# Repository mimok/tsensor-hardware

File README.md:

# tsensor-hardware
Kicad project of the Tsensor board

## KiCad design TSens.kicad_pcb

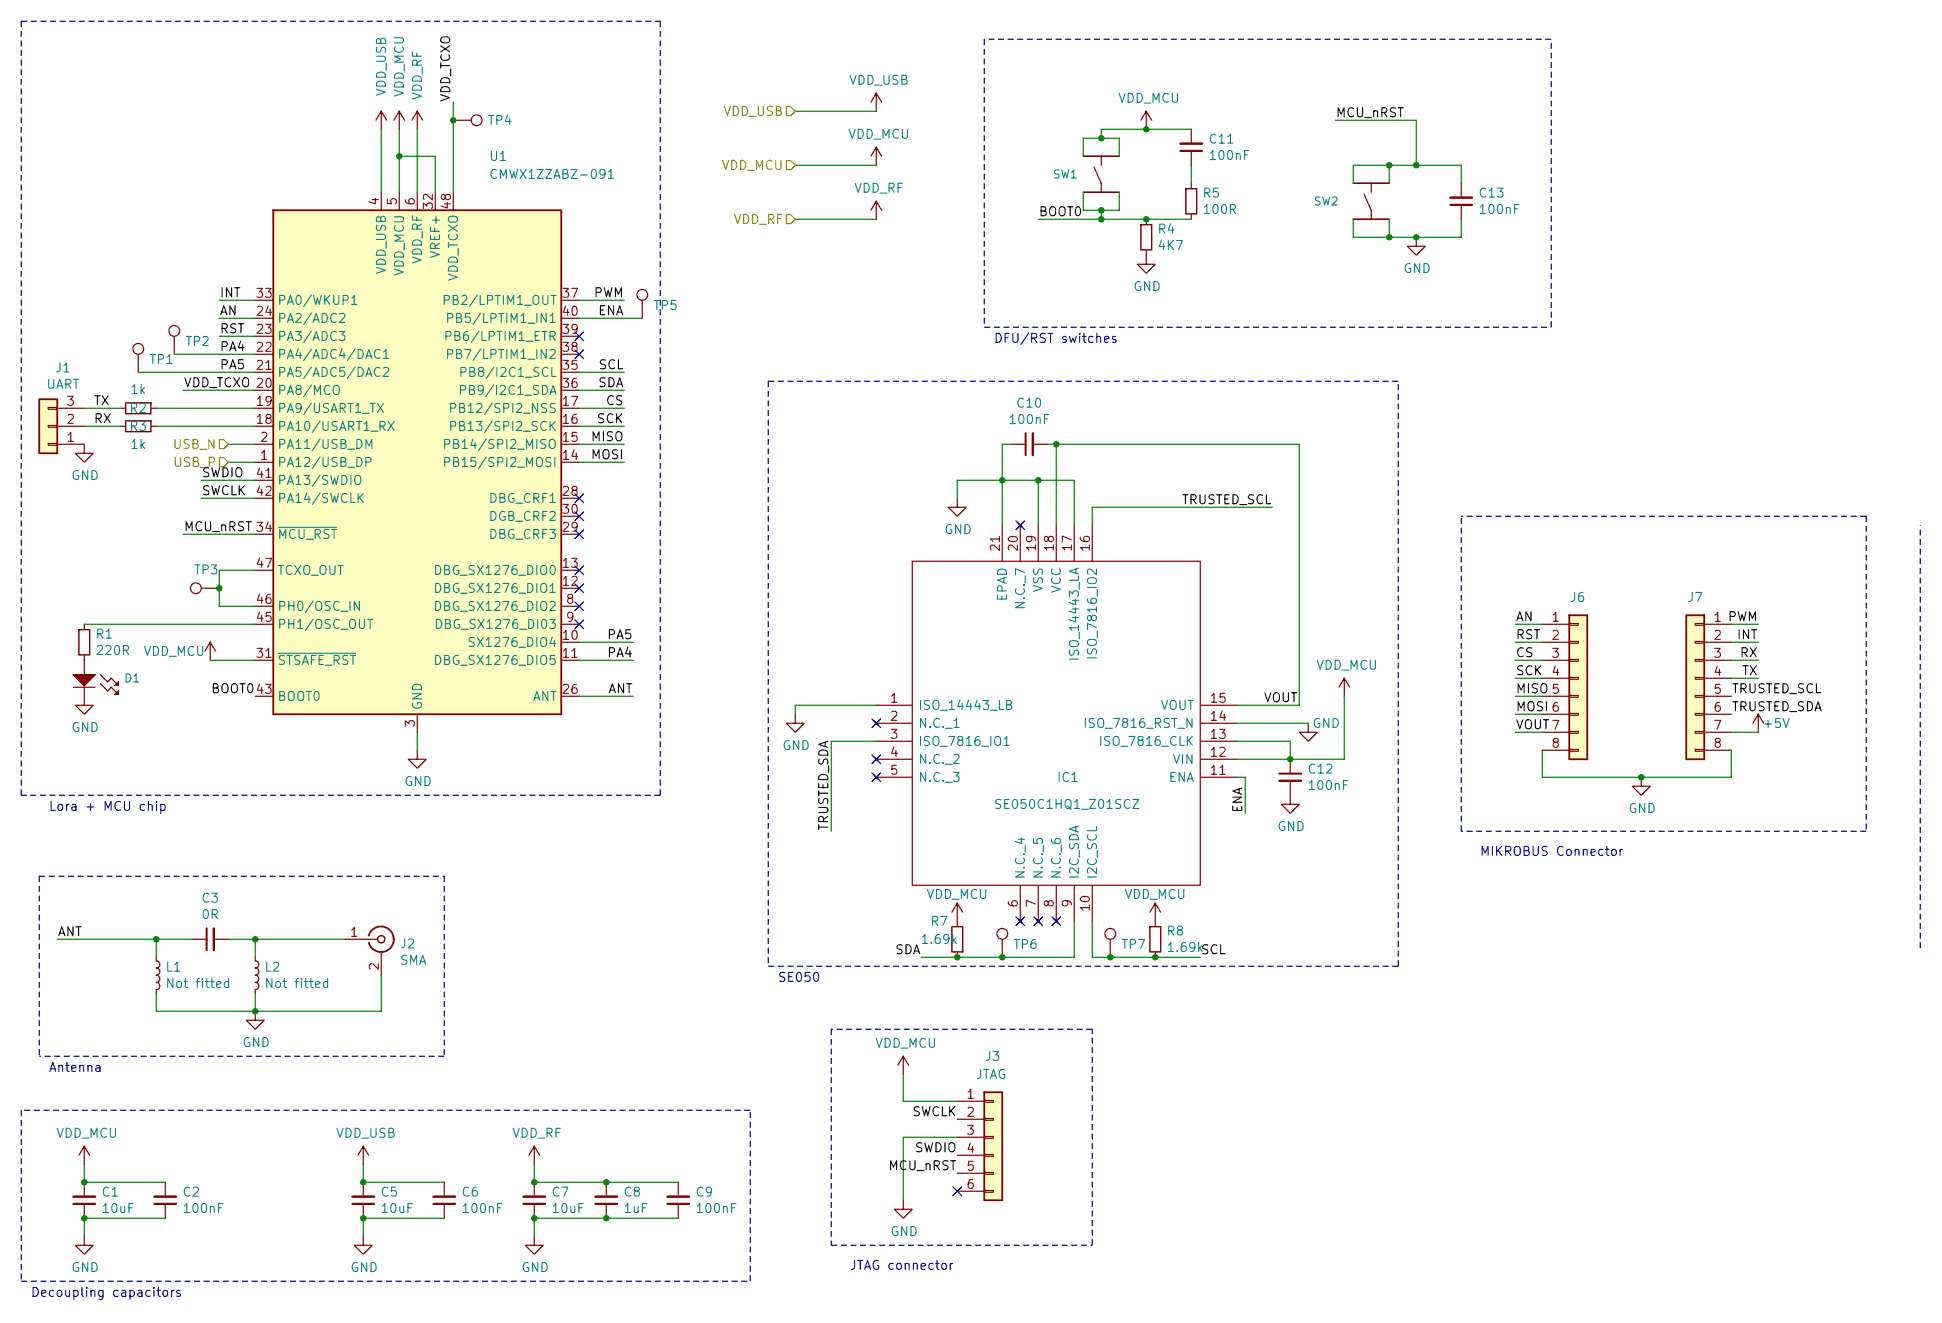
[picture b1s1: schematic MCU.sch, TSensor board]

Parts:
C1, C5, C7: 10uF; C_0603; Manufacturer_Part_Number GRM188R60J106KE47D; Mouser Part Number 81-GRM188R60J106KE7D
C2, C6, C9, C10, C11, C12, C13: 100nF; C_0603; Manufacturer_Part_Number 885012206020; Mouser Part Number 710-885012206020
C3: 0R; R_0603; Manufacturer_Part_Number RC0603JR-070RL; Mouser Part Number 603-RC0603JR-070RL
C8: 1uF; C_0603; Manufacturer_Part_Number C0603C105K8RACTU; Mouser Part Number 80-C0603C105K8RACTU
D1: LED_SINGLE-0603-RED; MF_LEDs-LED0603
IC1: SE050C1HQ1_Z01SCZ; QFN40P300X300X33-21N-D; Manufacturer_Part_Number SE050C1HQ1/Z01SCZ; Mouser Part Number 771-SE050C1HQ1Z01SCZ
J1: UART; PinHeader_1x03_P2.54mm_Vertical; Manufacturer_Part_Number M20-9990346; Mouser Part Number 855-M20-9990346
J2: SMA; SMA_Samtec_SMA-J-P-X-ST-EM1_EdgeMount; Manufacturer_Part_Number SMA-J-P-H-ST-EM1; Mouser Part Number 200-SMAJPHSTEM1
J3: JTAG; PinHeader_1x06_P2.54mm_Vertical; Manufacturer_Part_Number M20-9990646; Mouser Part Number 855-M20-9990646
J6, J7: Conn_01x08; PinSocket_1x08_P2.54mm_Vertical
L1, L2: Not fitted; L_0603
R1: 220R; R_0603; Manufacturer_Part_Number CRCW0603750RJNEA; Mouser Part Number 71-CRCW0603J-750-E3
R2, R3: 1k; R_0603; Manufacturer_Part_Number CRCW06031K00JNEAC; Mouser Part Number 71-CRCW06031K00JNEAC
R4: 4K7; R_0603; Manufacturer_Part_Number CRCW06034K70JNEAC; Mouser Part Number 71-CRCW06034K70JNEAC
R5: 100R; R_0603; Manufacturer_Part_Number CRCW0603100RJNEAC; Mouser Part Number 71-CRCW0603100RJNEAC
R7, R8: 1.69k; R_0603
SW1, SW2: TACT_4.2MM; MF_Switches-TACT4.2MM
TP1, TP2, TP3, TP4, TP5, TP6, TP7: TestPoint; TestPoint_Pad_D1.0mm
U1: CMWX1ZZABZ-091; MODULE_CMWX1ZZABZ-091; Manufacturer_Part_Number CMWX1ZZABZ-091; Mouser Part Number 81-CMWX1ZZABZ-091

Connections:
+3V3: C1.2, C2.2, C5.2, C6.2, C11.2, C12.1, IC1.12 (VIN), IC1.13 (ISO_7816_CLK), J3.1, R7.2, R8.1, SW1.1, SW1.2, U1.4 (VDD_USB), U1.5 (VDD_MCU), U1.31 (~STSAFE_RST), U1.32 (VREF+); also elsewhere on the board
+5V: J7.7; also elsewhere on the board
/MCU/AN: J6.1, U1.24 (PA2/ADC2)
/MCU/ANT: C3.1, L1.1, U1.26 (ANT)
/MCU/BOOT0: R4.1, R5.2, SW1.3, SW1.4, U1.43 (BOOT0)
/MCU/CS: J6.3, U1.17 (PB12/SPI2_NSS)
/MCU/ENA: IC1.11 (ENA), TP5.1, U1.40 (PB5/LPTIM1_IN1)
/MCU/INT: J7.2, U1.33 (PA0/WKUP1)
/MCU/MCU_nRST: C13.2, J3.5, SW2.1, SW2.2, U1.34 (~MCU_RST)
/MCU/MISO: J6.5, U1.15 (PB14/SPI2_MISO)
/MCU/MOSI: J6.6, U1.14 (PB15/SPI2_MOSI)
/MCU/PA4: TP2.1, U1.11 (DBG_SX1276_DIO5), U1.22 (PA4/ADC4/DAC1)
/MCU/PA5: TP1.1, U1.10 (SX1276_DIO4), U1.21 (PA5/ADC5/DAC2)
/MCU/PWM: J7.1, U1.37 (PB2/LPTIM1_OUT)
/MCU/RST: J6.2, U1.23 (PA3/ADC3)
/MCU/RX: J1.2, J7.3, R3.2
/MCU/SCK: J6.4, U1.16 (PB13/SPI2_SCK)
/MCU/SCL: IC1.10 (I2C_SCL), R8.2, TP7.1, U1.35 (PB8/I2C1_SCL)
/MCU/SDA: IC1.9 (I2C_SDA), R7.1, TP6.1, U1.36 (PB9/I2C1_SDA)
/MCU/SWCLK: J3.2, U1.42 (PA14/SWCLK)
/MCU/SWDIO: J3.4, U1.41 (PA13/SWDIO)
/MCU/TRUSTED_SCL: IC1.16 (ISO_7816_IO2), J7.5
/MCU/TRUSTED_SDA: IC1.3 (ISO_7816_IO1), J7.6
/MCU/TX: J1.3, J7.4, R2.2
/MCU/USB_N: U1.2 (PA11/USB_DM); also elsewhere on the board
/MCU/USB_P: U1.1 (PA12/USB_DP); also elsewhere on the board
/MCU/VDD_TCXO: TP4.1, U1.20 (PA8/MCO), U1.48 (VDD_TCXO)
/MCU/VOUT: C10.2, IC1.15 (VOUT), IC1.18 (VCC), J6.7
GND: C1.1, C2.1, C5.1, C6.1, C7.1, C8.1, C9.1, C10.1, C12.2, C13.1, D1.CATH (CATHODE), IC1.1 (ISO_14443_LB), IC1.14 (ISO_7816_RST_N), IC1.17 (ISO_14443_LA), IC1.19 (VSS), IC1.21 (EPAD), J1.1, J2.2 (Ext), J3.3, J6.8, J7.8, L1.2, L2.2, R4.2, SW2.3, SW2.4, U1.3 (GND), U1.7 (GND), U1.25 (GND), U1.27 (GND), U1.44 (GND), U1.49 (GND), U1.50 (GND), U1.51 (GND), U1.52 (GND), U1.53 (GND), U1.54 (GND), U1.55 (GND), U1.56 (GND), U1.57 (GND); also elsewhere on the board
unnamed: C3.2, J2.1 (In), L2.1
unnamed: C11.1, R5.1
unnamed: D1.ANOD (ANODE), R1.2
unnamed: R1.1, U1.45 (PH1/OSC_OUT)
unnamed: R2.1, U1.19 (PA9/USART1_TX)
unnamed: R3.1, U1.18 (PA10/USART1_RX)
unnamed: TP3.1, U1.46 (PH0/OSC_IN), U1.47 (TCXO_OUT)
VDD_RF: C7.2, C8.2, C9.2, U1.6 (VDD_RF); also elsewhere on the board

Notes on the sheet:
DFU/RST switches
Decoupling capacitors
MIKROBUS Connector
JTAG connector
Antenna
SE050
Lora + MCU chip

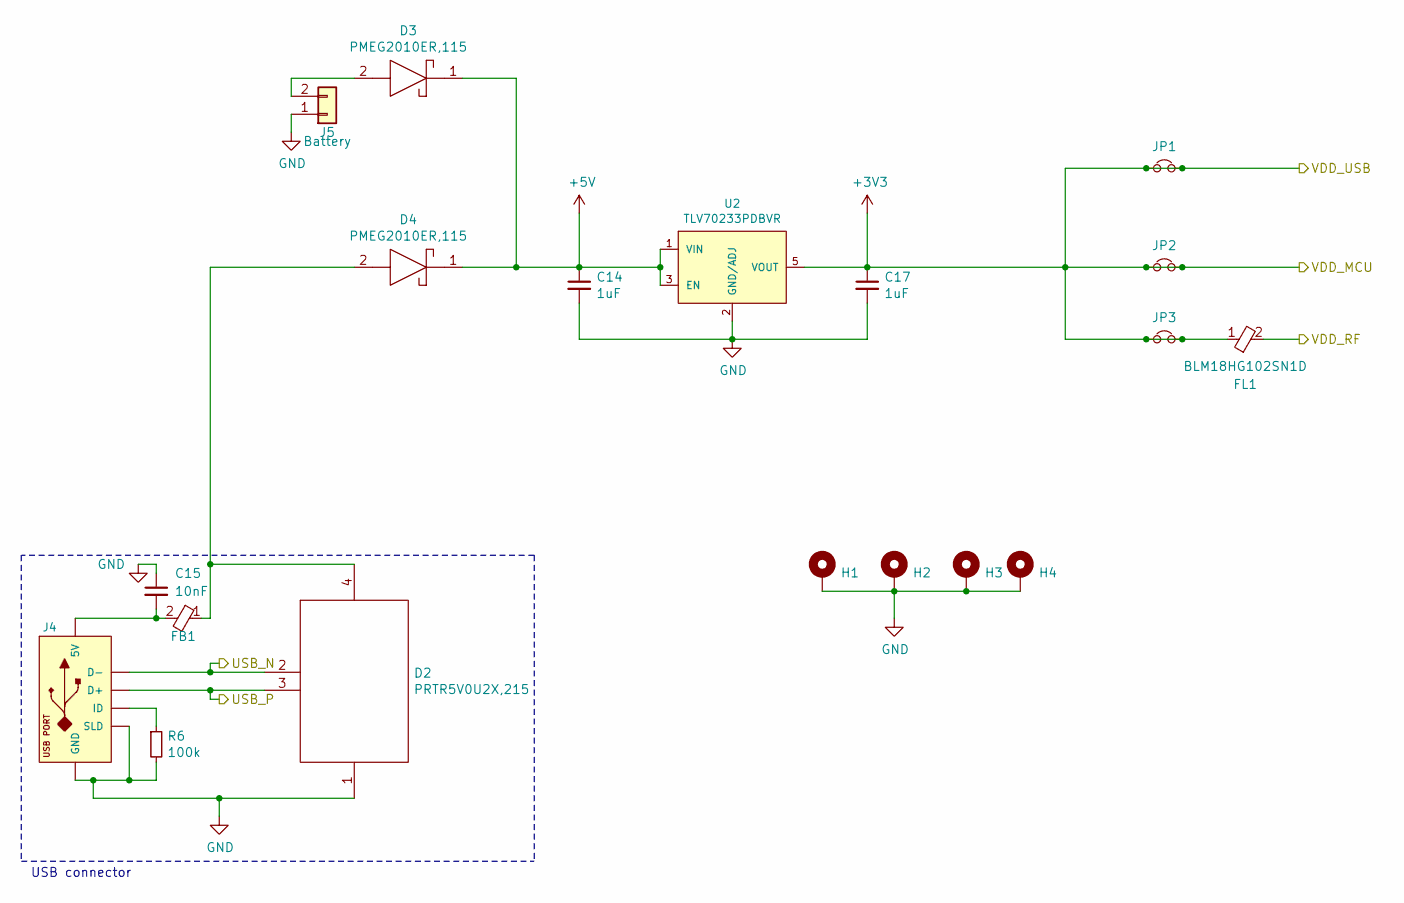
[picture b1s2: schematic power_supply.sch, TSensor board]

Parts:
C14, C17: 1uF; C_0603; Manufacturer_Part_Number C0603C105K8RACTU; Mouser Part Number 80-C0603C105K8RACTU
C15: 10nF; C_0603; Manufacturer_Part_Number 885012206014; Mouser Part Number 710-885012206014
D2: PRTR5V0U2X,215; SOT-143B; Mouser Part Number 771-PRTR5V0U2X-T/R
D3, D4: PMEG2010ER,115; SODFL3517X110N; Mouser Part Number 771-PMEG2010ER115
FB1: BK0603HS330-T; BEADC0603X33N; Mouser Part Number 963-BK0603HS330-T
FL1: BLM18HG102SN1D; BEADC1608X95N; Mouser Part Number 81-BLM11HA102SG
H1, H2, H3, H4: MountingHole_Pad; MountingHole_2.2mm_M2
J4: USB_MICRO_RIGHT; MF_Connectors-MICROUSB-RIGHT
J5: Battery; JST_PH_B2B-PH-SM4-TB_02x2.00mm_Straight; Manufacturer_Part_Number B2B-PH-SM4-TB(LF)(SN)
JP1, JP2, JP3: Jumper_NC_Small; PinHeader_1x02_P2.54mm_Vertical; Manufacturer_Part_Number M20-9990246; Mouser Part Number 855-M20-9990246
R6: 100k; R_0603; Manufacturer_Part_Number CRCW0603100KJNEAC; Mouser Part Number 71-CRCW0603100KJNEAC
U2: TLV70233PDBVR; MF_IC_Power-SOT-23-5

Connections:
+3V3: C17.1, FL1.1, JP1.1, JP1.2, JP2.1, JP2.2, JP3.1, JP3.2, U2.5 (VOUT); also elsewhere on the board
+5V: C14.1, D3.1, D4.1, U2.1 (VIN), U2.3 (EN); also elsewhere on the board
/MCU/USB_N: D2.2, J4.2 (D-); also elsewhere on the board
/MCU/USB_P: D2.3, J4.3 (D+); also elsewhere on the board
GND: C14.2, C15.1, C17.2, D2.1, H1.1, H2.1, H3.1, H4.1, J4.5 (GND), J4.S1 (SLD), J4.S2 (SLD), J4.S3 (SLD), J4.S4 (SLD), J4.S5 (SLD), J4.S6 (SLD), J5.1, R6.2, U2.2 (GND/ADJ); also elsewhere on the board
unnamed: C15.2, FB1.2, J4.1 (5V)
unnamed: D2.4, D4.2, FB1.1
unnamed: D3.2, J5.2
unnamed: J4.4 (ID), R6.1
VDD_RF: FL1.2; also elsewhere on the board

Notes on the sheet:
USB connector

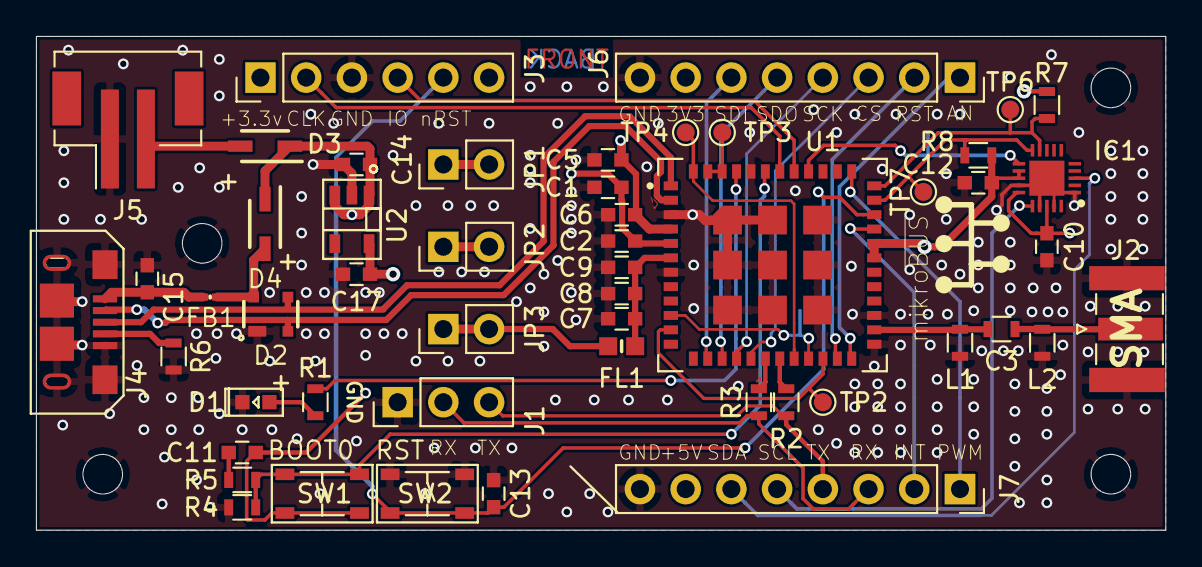
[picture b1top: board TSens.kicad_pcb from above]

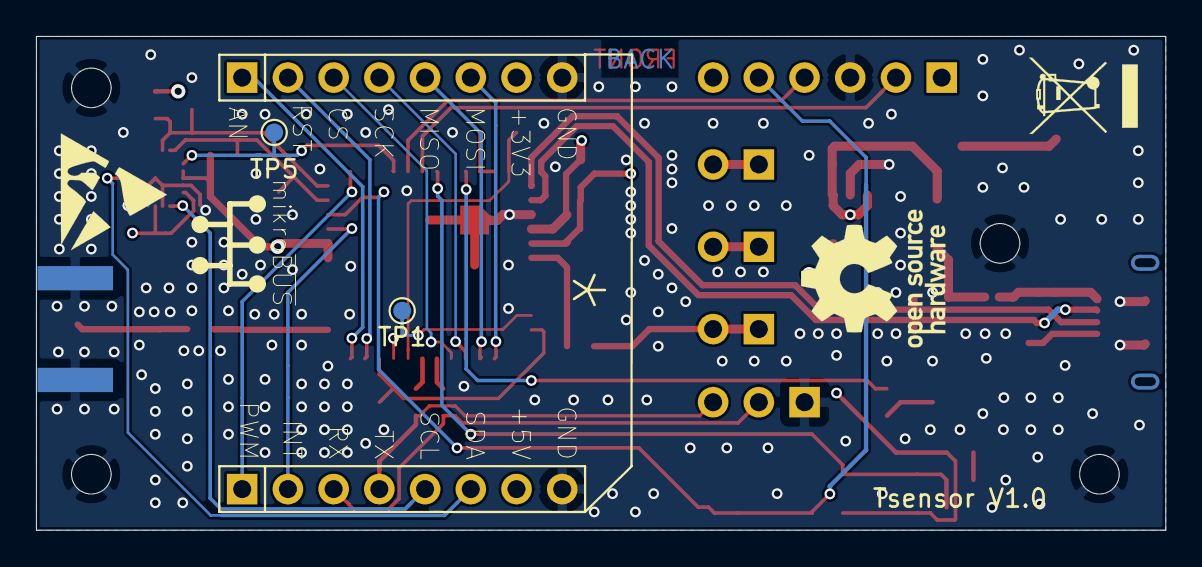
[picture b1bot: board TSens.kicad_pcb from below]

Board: 4 copper layers, 62.7 x 27.4 mm, 58 parts (2 on the bottom side), 41 nets.

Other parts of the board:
CON1: MIKROBUS_HOST_CONN; MIKROBUS_CONN

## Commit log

2020-05-18 Add license file
    All this work is licensed unde CC-BY-4.0.
